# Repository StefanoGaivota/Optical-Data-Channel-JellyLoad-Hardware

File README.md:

Jelly Load is touted as one of the most inconvenient (but also most fun) ways of loading data into your 8 bit computer.<br>
The concept is the collaborative creation of Dave Curran (Tynemouth Software) and Rod Hull (The Future Was 8 bit).

<br>
Data and clock signals are encoded into a video stream as a matrix of black or white areas.<br>
The receiving interface senses the optical channel bit state and converts the result into an 8 bit data word
for interpretation by the target computer upon receiving valid clock edge.

Take a look here:<br>
https://www.tfw8b.com/introducing-jelly-load/<br>
for a historical account.

The loader binaries for VIC20 can be found here:<br>
https://www.tfw8b.com/wp-content/uploads/2024/09/JellyLoad-VIC20-240908.zip<br>
(different ones depending upon your RAM configuration)

This repository is my own effort at creating a JellyLoad receive interface for Commodore computer user port.

It comprises two separate boards which connect to each other via a 14way IDC cable assembly along with associated opto-mechanical components.<br>
KiCAD source is available for schematic and PCB of each board.<br>
FreeCAD source is available for the mechanical elements (Optical Housing and Monitor Guide).<br>
Manufacturing data generated from these sources is detailed later in this document.<br><br>
<p><u><b>Printed Circuit Board parts</u></b></p><br>

* Optical Interface board:

Phototransistors are arranged in the required matrix, photocurrent converted to voltage at input of Schmitt inverter. Inverter outputs are routed to 14 Way IDC.<br>
Clock signal is indicated by an LED for visual feedback of correct operation.<br>
Originally developed to use the OSRAM SFH3710 phototransistor, this seems to be superceded by the SFH3716 (as of December 2025).  Should be a drop-in replacement but YMMV.
<br><br>

* Target Interface board:

Target interface connects the 14Way IDC pins and routes logic signals to target computer User Port connector.<br>
Solder blob config pads route the CLK signal to the user port pin required by the target computer.<br>
This differs between PET, VIC20 and C64. Blob your required option.<br>
Board profile is configured to fit inside a C64 cartridge case.<br>
Case mechanics are shown on layer User.Eco1.<br>
PDF of machining dimensions is made available for convenience.<br><br>
<br>
<p><u><b>Mechanical components</u></b></p><br>

* Optical Housing:

The Optical Interface board is fitted with this Optical Housing for the purpose of reducing ambient light interference and to help align with the optical channel.<br>
Optical aperture adaptors (glass spheres) are accommodated in this section to match the sensor aperture to the available width. A specification for suitable spheres is available in the mechanical data directory. Basically 6.0mm glass balls of good optical clarity.<br>
The graphical calculations shown here are based on a refractive index of 1.4.<br>

<br>
The sensor array will work adequately without the aperture adaptors but sensitivity will be reduced so you will need to use higher monitor brightness for reliable transmission. <br>
The housing can be secured to the sensor board with your adhesive of choice, (sticky tape, cyanoacrylate, blu-tack, toffee etc) or careful heat-staking of the retaining lugs.<br><br>

* Monitor Guide:

The Monitor Guide is attached to the receiving monitor screen, aligned with the appropriately scaled JellyLoad optical channel.<br><br>

<p><u><b>Manufacturing Data</u></b></p><br>

Manufacturing Data for production of Printed Circuit Boards and 3D printed mechanics is available in the "Manufacturing Data" folder.<br>

Bill-Of-Materials (BOM) with Digikey stock codes. BOM and pick/place files for use with JLC (A cheap and cheerful PCB Assembly company)<br>
Gerber+Drill zip for PCB manufacture.<br>

Assembly tooling holes are 1.152mm top-left and bottom right of layout. With JLC, specify "Tooling holes added by customer" at assembly stage.<br><br>

STL exports of Optical Housing and Monitor Guide can be used with most additive manufacturing processes.<br><br>

Once assembled, it should all look something like this:<br>

<br>

Then it's time to connect it up and try it out.<br>
Adjust monitor brightness to give reliable transition of CLOCK LED when presented with light or dark segments at the monitor.<br>
A usable Paint application is your friend here!
<br><br>
A selection of JellyLoad encoded videos can be found here:<br>
https://www.youtube.com/playlist?list=PLbE6E7xnjkkJwXpoj5DF8uXBsocBH2ZH-
<br><br>

Please feel free to get in touch if there's anything you'd like to ask about relating to this repository.<br>
I'm on:<br>
Bluesky  https://bsky.app/profile/stefanogaivota.bsky.social <br>
and <br>
Fedi     https://universeodon.com/@StefanoGaivota<br>
<br>
Best of luck!

</body>

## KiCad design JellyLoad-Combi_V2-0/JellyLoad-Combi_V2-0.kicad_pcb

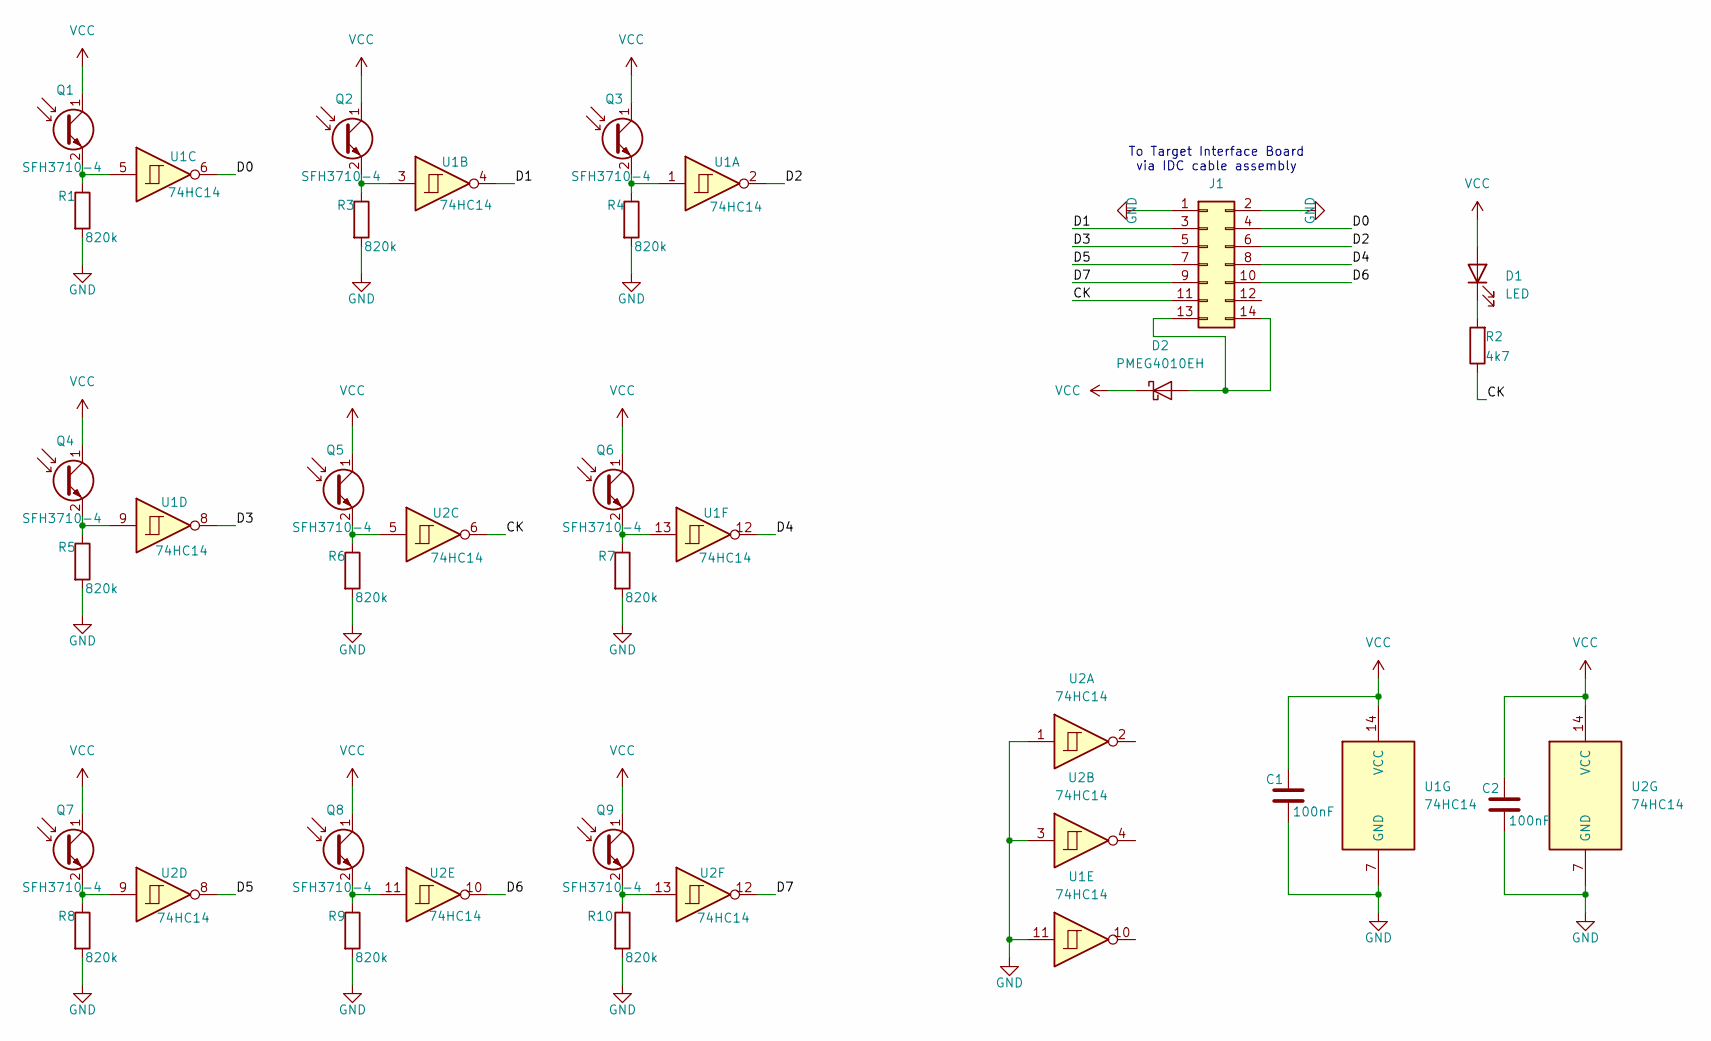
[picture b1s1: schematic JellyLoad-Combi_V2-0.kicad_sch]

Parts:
C1, C2: 100nF; C_0402_1005Metric
D1: LED; LED_0603_1608Metric; JLC PN C19273151
D2: PMEG4010EH; D_SOD-123F; JLC PN C2999987
J1: Conn_02x07_Odd_Even; IDC-Header_2x07_P2.54mm_Vertical; JLC PN C11215
Q1, Q2, Q3, Q4, Q5, Q6, Q7, Q8, Q9: SFH3710-4; Osram_SFH3710
R1, R3, R4, R5, R6, R7, R8, R9, R10: 820k; R_0402_1005Metric; JLC PN C144706
R2: 4k7; R_0402_1005Metric; JLC PN C138287
U1, U2: 74HC14; TSSOP-14_4.4x5mm_P0.65mm; JLC PN C6821

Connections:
/CK: J1.11, R2.1, U2.6
/D0: J1.4, U1.6
/D1: J1.3, U1.4
/D2: J1.6, U1.2
/D3: J1.5, U1.8
/D4: J1.8, U1.12
/D5: J1.7, U2.8
/D6: J1.10, U2.10
/D7: J1.9, U2.12
GND: C1.2, C2.2, J1.1, J1.2, R1.2, R3.2, R4.2, R5.2, R6.2, R7.2, R8.2, R9.2, R10.2, U1.7 (GND), U1.11, U2.1, U2.3, U2.7 (GND)
unnamed: D1.1 (K), R2.2
unnamed: D2.2 (A), J1.13, J1.14
unnamed: Q1.2 (E), R1.1, U1.5
unnamed: Q2.2 (E), R3.1, U1.3
unnamed: Q3.2 (E), R4.1, U1.1
unnamed: Q4.2 (E), R5.1, U1.9
unnamed: Q5.2 (E), R6.1, U2.5
unnamed: Q6.2 (E), R7.1, U1.13
unnamed: Q7.2 (E), R8.1, U2.9
unnamed: Q8.2 (E), R9.1, U2.11
unnamed: Q9.2 (E), R10.1, U2.13
VCC: C1.1, C2.1, D1.2 (A), D2.1 (K), Q1.1 (C), Q2.1 (C), Q3.1 (C), Q4.1 (C), Q5.1 (C), Q6.1 (C), Q7.1 (C), Q8.1 (C), Q9.1 (C), U1.14 (VCC), U2.14 (VCC)

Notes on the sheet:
To Target Interface Board via IDC cable assembly

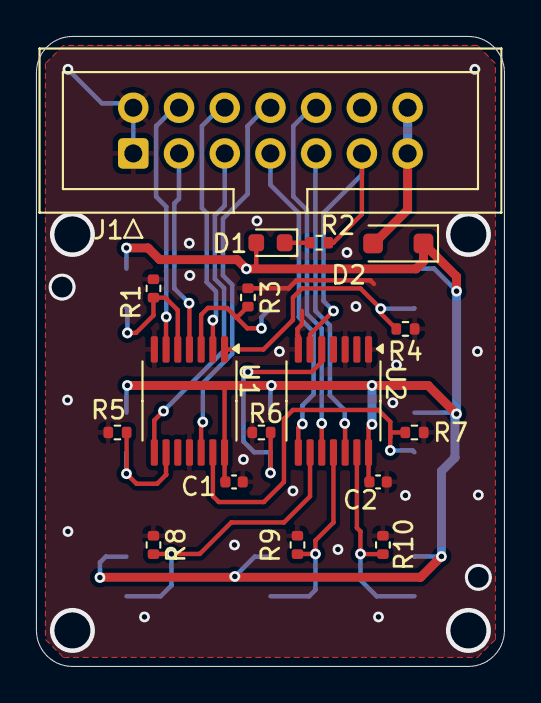
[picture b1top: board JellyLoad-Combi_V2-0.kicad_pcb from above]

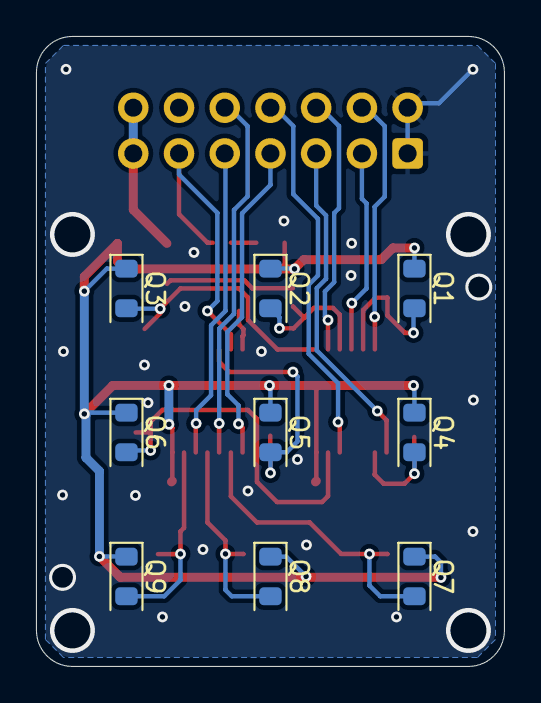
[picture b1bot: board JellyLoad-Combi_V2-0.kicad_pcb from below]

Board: 2 copper layers, 26.0 x 35.0 mm, 26 parts (9 on the bottom side), 22 nets.

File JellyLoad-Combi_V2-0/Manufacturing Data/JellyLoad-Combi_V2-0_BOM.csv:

"Reference","Value","Qty","JLC PN","DK-PN"
"C1,C2","100nF","2","","490-6328-1-ND"
"D1","LED","1","C19273151","732-4978-1-ND"
"D2","PMEG4010EH","1","C2999987","1727-3880-1-ND"
"J1","Conn_02x07_Odd_Even","1","C11215","2987-CH87142V201-ND"
"Q1,Q2,Q3,Q4,Q5,Q6,Q7,Q8,Q9","SFH3710-4","9","","475-SFH3710-3/4-ZCT-ND"
"R1,R3,R4,R5,R6,R7,R8,R9,R10","820k","9","C144706",""
"R2","4k7","1","C138287",""
"U1,U2","74HC14","2","C6821","296-8234-1-ND"

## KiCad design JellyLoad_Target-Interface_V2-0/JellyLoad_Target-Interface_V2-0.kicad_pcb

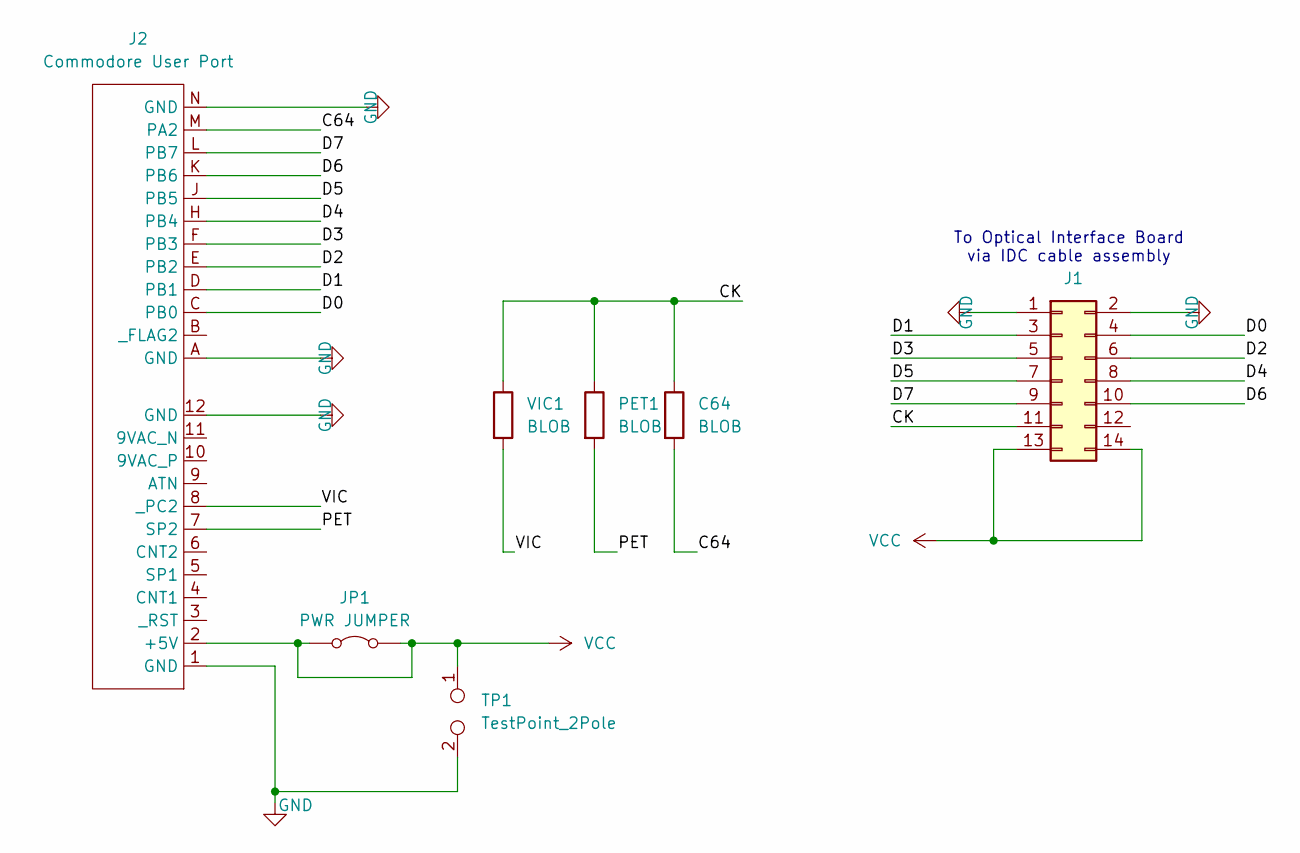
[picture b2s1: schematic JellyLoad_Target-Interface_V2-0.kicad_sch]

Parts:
C64: BLOB; SolderJumper-2_P1.3mm_Open_RoundedPad1.0x1.5mm
J1: Conn_02x07_Odd_Even; IDC-Header_2x07_P2.54mm_Vertical; JLC PN 571-1761681-5
J2: Commodore User Port; Commodore-UserPort-Connector; JLC PN 587-307-024 (Stupidly expensive, try Sw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
JP1: PWR JUMPER; R_1206_3216Metric
PET1: BLOB; SolderJumper-2_P1.3mm_Open_RoundedPad1.0x1.5mm
TP1: TestPoint_2Pole; PinHeader_1x02_P2.54mm_Vertical
VIC1: BLOB; SolderJumper-2_P1.3mm_Open_RoundedPad1.0x1.5mm

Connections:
/C64: C64.2, J2.M (PA2)
/CK: C64.1, J1.11, PET1.1, VIC1.1
/D0: J1.4, J2.C (PB0)
/D1: J1.3, J2.D (PB1)
/D2: J1.6, J2.E (PB2)
/D3: J1.5, J2.F (PB3)
/D4: J1.8, J2.H (PB4)
/D5: J1.7, J2.J (PB5)
/D6: J1.10, J2.K (PB6)
/D7: J1.9, J2.L (PB7)
/PET: J2.7 (SP2), PET1.2
/VIC: J2.8 (_PC2), VIC1.2
GND: J1.1, J1.2, J2.1 (GND), J2.12 (GND), J2.A (GND), J2.N (GND), TP1.2
VCC: J1.13, J1.14, J2.2 (+5V), JP1.1 (A), JP1.2 (B), TP1.1

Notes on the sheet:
To Optical Interface Board via IDC cable assembly

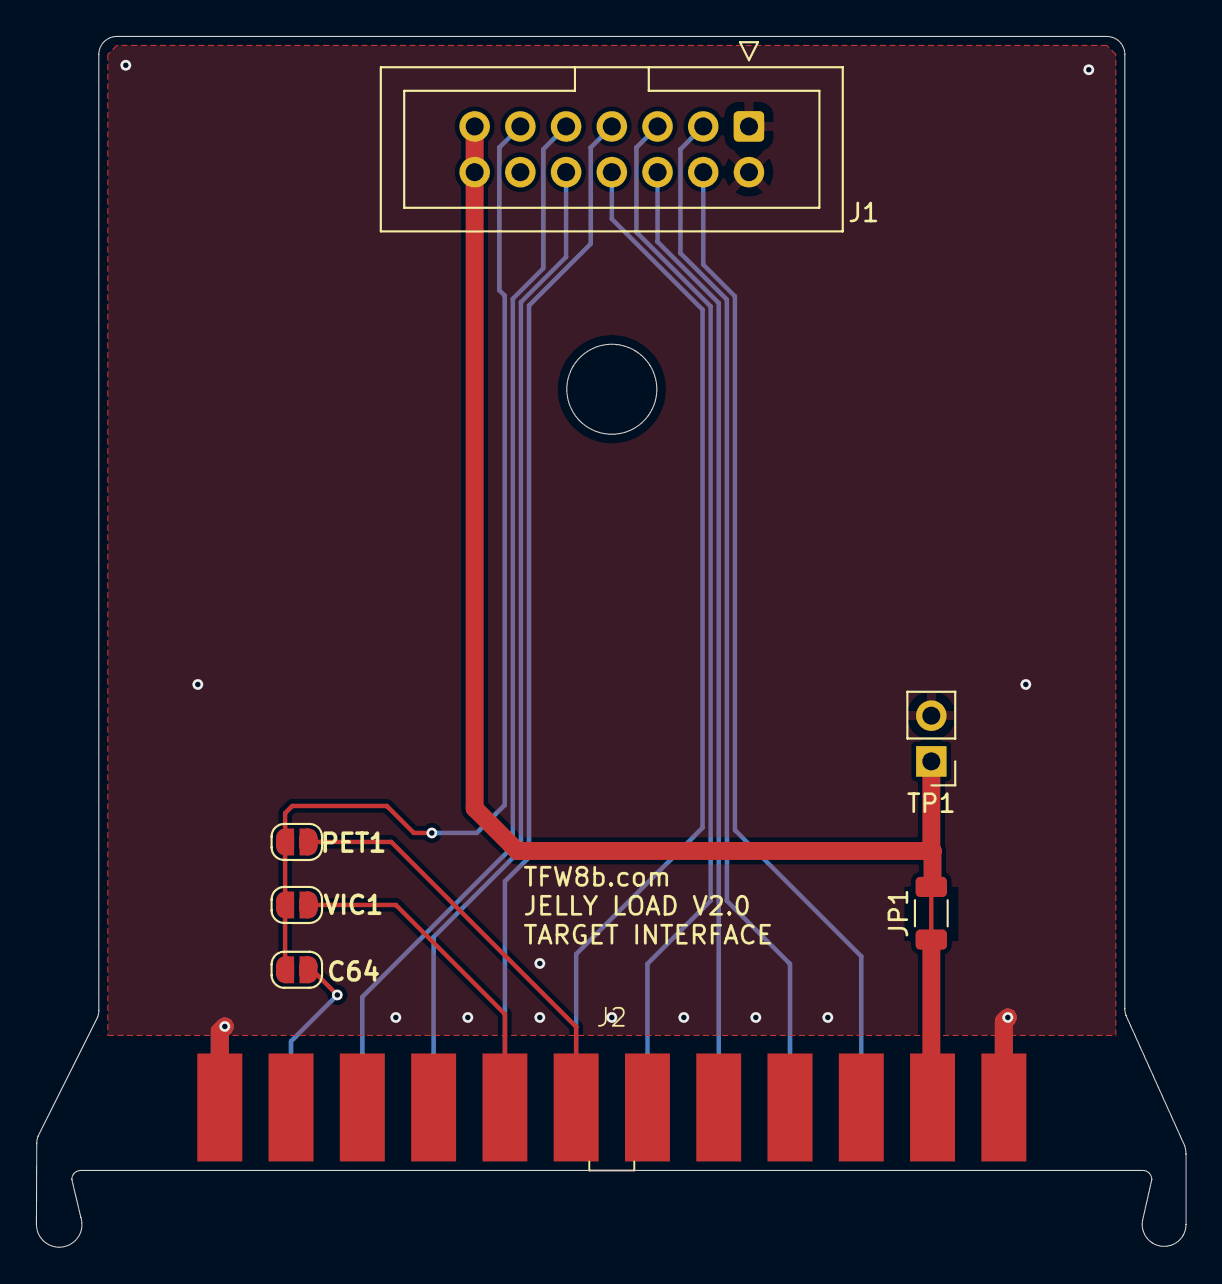
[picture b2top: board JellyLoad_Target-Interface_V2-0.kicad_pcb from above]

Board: 2 copper layers, 63.9 x 67.3 mm, 7 parts (0 on the bottom side), 14 nets.

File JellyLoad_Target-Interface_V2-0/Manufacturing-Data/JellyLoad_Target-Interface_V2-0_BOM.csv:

Reference,Value,Qty,Mouser PN,
J1,Conn_02x07_Odd_Even,1,571-1761681-5,
J2,Commodore User Port,1,587-307-024  (Stupidly expensive, try Switch Electronics)

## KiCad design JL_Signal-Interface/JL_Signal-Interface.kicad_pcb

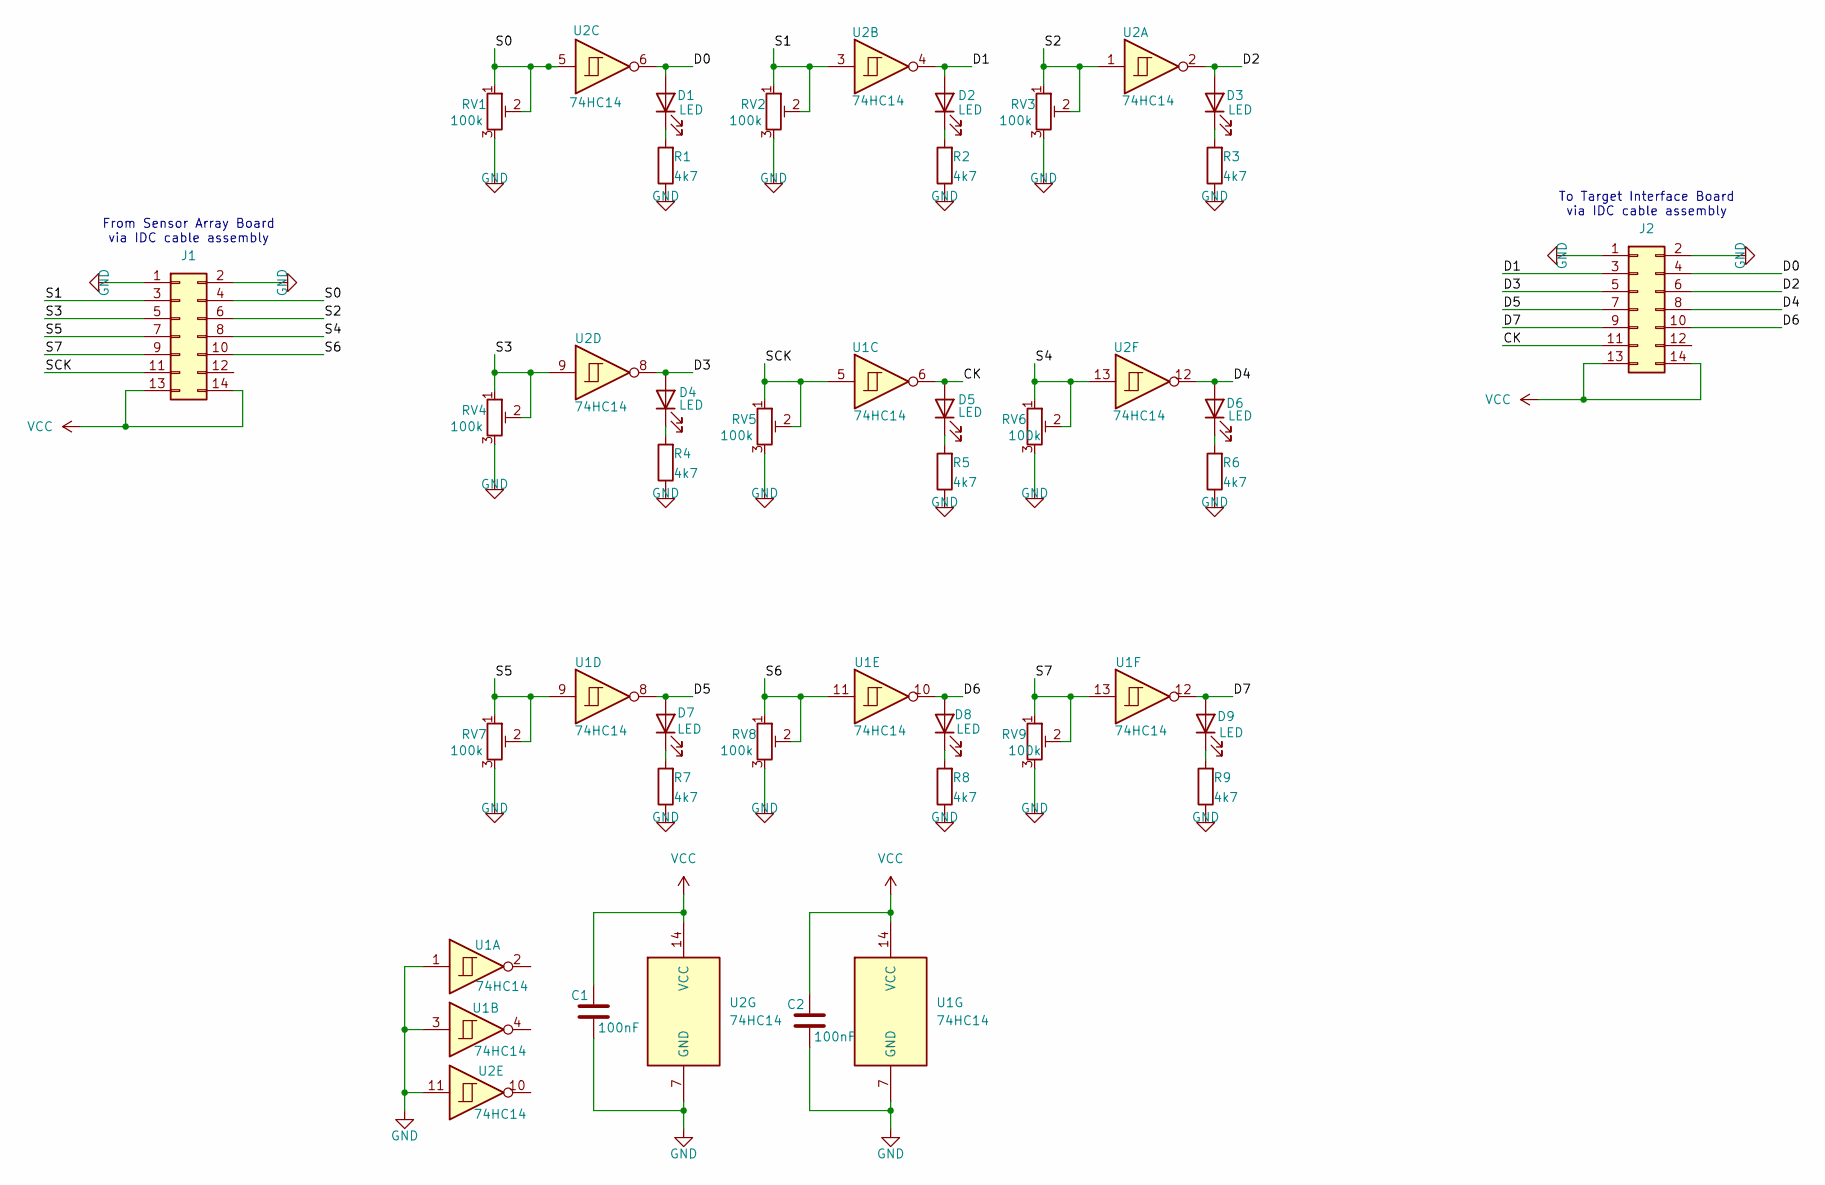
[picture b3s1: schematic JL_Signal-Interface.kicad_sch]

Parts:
C1, C2: 100nF; C_1206_3216Metric_Pad1.33x1.80mm_HandSolder; JLC PN 80-C1206C104K5R7800
D1, D2, D3, D4, D5, D6, D7, D8, D9: LED; LED_1206_3216Metric_Pad1.42x1.75mm_HandSolder; JLC PN 710-150120RS75000
J1, J2: IDC Header 14W; IDC-Header_2x07_P2.54mm_Vertical; JLC PN 571-1761681-5
R1, R2, R3, R4, R5, R6, R7, R8, R9: 4k7; R_1206_3216Metric_Pad1.30x1.75mm_HandSolder; JLC PN 603-RT1206FRE074K7L
RV1, RV2, RV3, RV4, RV5, RV6, RV7, RV8, RV9: 100k; Potentiometer_Bourns_3386F_Vertical; JLC PN 652-3306P-1-104
U1, U2: 74HC14; SOIC-14_3.9x8.7mm_P1.27mm; JLC PN 771-74HC14D-T

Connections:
/CK: D5.2 (A), J2.11, U1.6
/D0: D1.2 (A), J2.4, U2.6
/D1: D2.2 (A), J2.3, U2.4
/D2: D3.2 (A), J2.6, U2.2
/D3: D4.2 (A), J2.5, U2.8
/D4: D6.2 (A), J2.8, U2.12
/D5: D7.2 (A), J2.7, U1.8
/D6: D8.2 (A), J2.10, U1.10
/D7: D9.2 (A), J2.9, U1.12
/S0: J1.4, RV1.1, RV1.2, U2.5
/S1: J1.3, RV2.1, RV2.2, U2.3
/S2: J1.6, RV3.1, RV3.2, U2.1
/S3: J1.5, RV4.1, RV4.2, U2.9
/S4: J1.8, RV6.1, RV6.2, U2.13
/S5: J1.7, RV7.1, RV7.2, U1.9
/S6: J1.10, RV8.1, RV8.2, U1.11
/S7: J1.9, RV9.1, RV9.2, U1.13
/SCK: J1.11, RV5.1, RV5.2, U1.5
GND: C1.2, C2.2, J1.1, J1.2, J2.1, J2.2, R1.1, R2.1, R3.1, R4.1, R5.1, R6.1, R7.1, R8.1, R9.1, RV1.3, RV2.3, RV3.3, RV4.3, RV5.3, RV6.3, RV7.3, RV8.3, RV9.3, U1.1, U1.3, U1.7 (GND), U2.7 (GND), U2.11
unnamed: D1.1 (K), R1.2
unnamed: D2.1 (K), R2.2
unnamed: D3.1 (K), R3.2
unnamed: D4.1 (K), R4.2
unnamed: D5.1 (K), R5.2
unnamed: D6.1 (K), R6.2
unnamed: D7.1 (K), R7.2
unnamed: D8.1 (K), R8.2
unnamed: D9.1 (K), R9.2
VCC: C1.1, C2.1, J1.13, J1.14, J2.13, J2.14, U1.14 (VCC), U2.14 (VCC)

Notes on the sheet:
To Target Interface Board via IDC cable assembly
From Sensor Array Board via IDC cable assembly

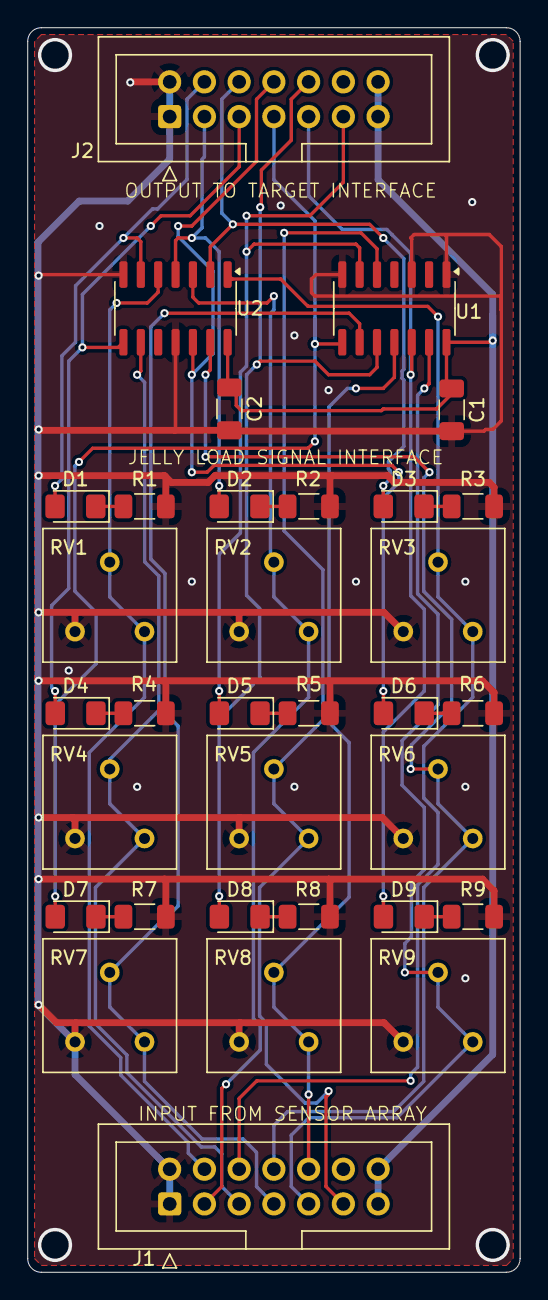
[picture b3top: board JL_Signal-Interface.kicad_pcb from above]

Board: 2 copper layers, 36.0 x 91.0 mm, 33 parts (0 on the bottom side), 29 nets.

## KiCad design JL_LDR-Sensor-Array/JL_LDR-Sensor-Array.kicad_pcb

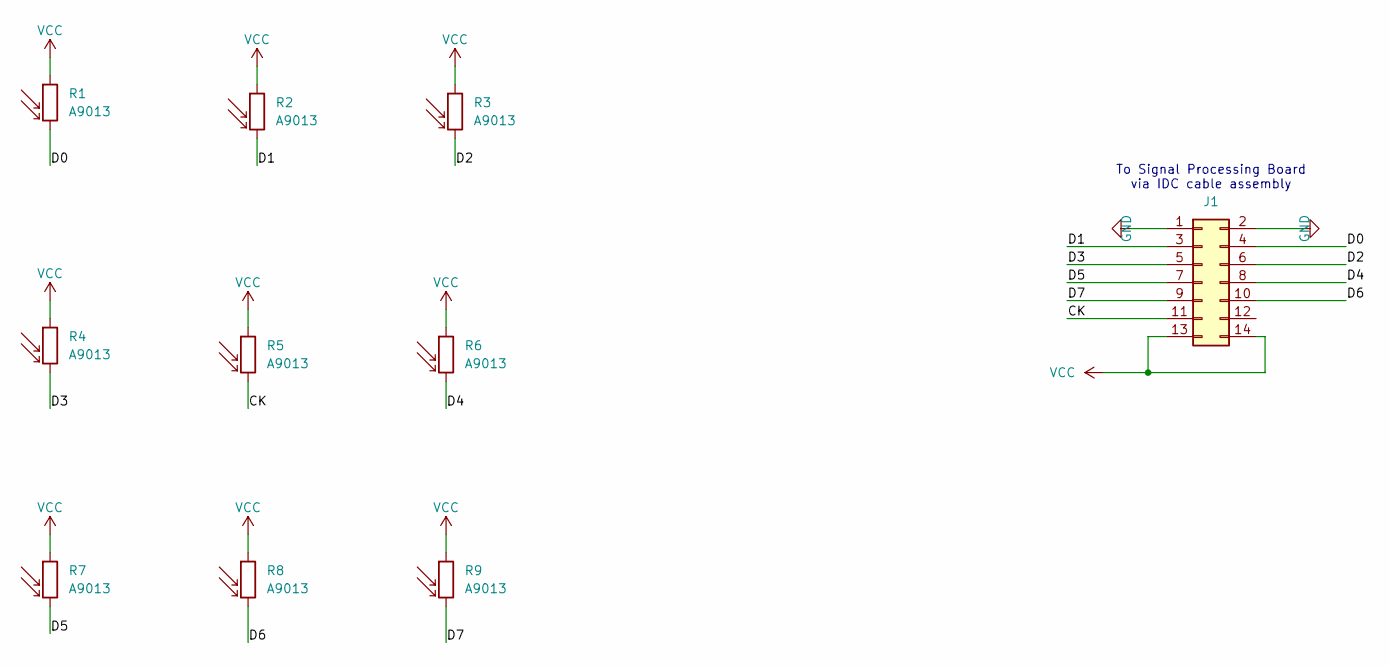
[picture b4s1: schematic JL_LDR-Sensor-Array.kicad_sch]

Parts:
J1: 14W IDC Header; IDC-Header_2x07_P2.54mm_Vertical; JLC PN 571-1761681-5
R1, R2, R3, R4, R5, R6, R7, R8, R9: A9013; R_LDR_5.0x4.1mm_P3mm_Vertical; JLC PN 846-PDV-P8104

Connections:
/CK: J1.11, R5.2
/D0: J1.4, R1.2
/D1: J1.3, R2.2
/D2: J1.6, R3.2
/D3: J1.5, R4.2
/D4: J1.8, R6.2
/D5: J1.7, R7.2
/D6: J1.10, R8.2
/D7: J1.9, R9.2
GND: J1.1, J1.2
VCC: J1.13, J1.14, R1.1, R2.1, R3.1, R4.1, R5.1, R6.1, R7.1, R8.1, R9.1

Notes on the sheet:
To Signal Processing Board via IDC cable assembly

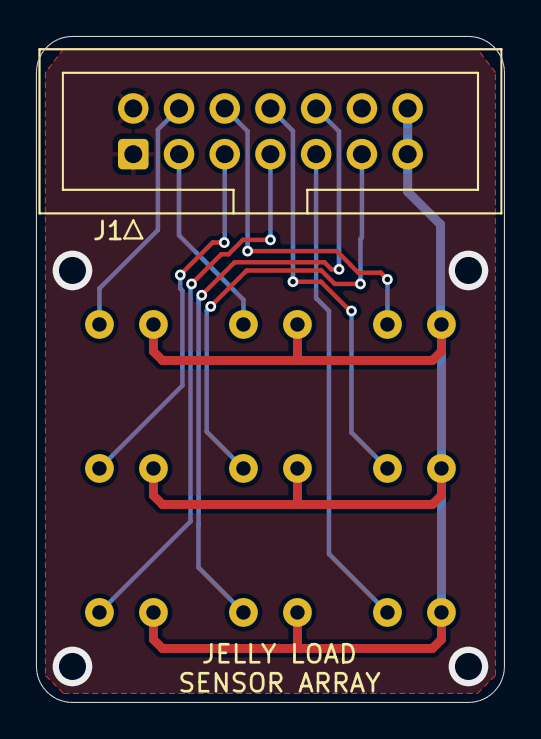
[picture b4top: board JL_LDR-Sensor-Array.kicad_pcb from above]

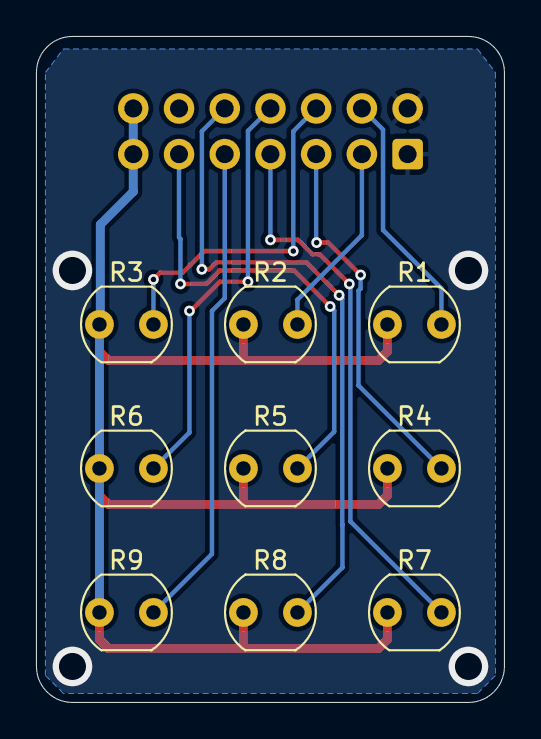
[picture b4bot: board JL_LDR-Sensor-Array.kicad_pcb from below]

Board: 2 copper layers, 26.0 x 37.0 mm, 10 parts (9 on the bottom side), 11 nets.

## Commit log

2024-10-09 KiCAD and manufacturing data uploaded
    LDR Sensor array, Signal Interface and Target Interface boards for JellyLoad system
2024-10-09 Update README.md
    Added some links and creative credits
2024-10-10 Example visualisation added
2024-10-10 Cartridge case machining dimensions
    Dimensions of required cutting for cartridge case to create aperture for IDC connector.
    Based on using 3.175mm diameter cutting tool.
    Reference position is with tool touching top right internal corner as viewed from ABOVE as in the CAD view.
    NOTE: this will be MIRRORED in real life with the case upside down on the toolbed, so ref position shown in this diagram will be TOP LEFT on the toolbed.
    Easier for you to do the mental gymnastics than to reconfigure CAD and end up with something even more confusing.
2024-10-10 Updated Mfr data with better assembly drawing
2024-10-11 Added Mechanical Data for Optical Housing etc
    FreeCAD part design for Jelly Load Optical Housing and Monitor Guide. Export of STL for each part for use in additive manufacture process.
2024-10-11 Updated README.md
    Tried to add GIF of Jelly Load video excerpt
2024-10-11 Update README.md
    Added illustrations of system elements.
    Added description of mechanical elements.
2024-10-11 Update README.md
    Formatted to show illustrations of system parts
2024-10-11 Update README.md
    Formatting update
2024-10-11 Update README.md
    Formatting updates
2024-10-11 Update README.md
    Formatting updates (third time's a charm?)
2024-10-11 Update README.md
    Formatting updates. Turns out third time wasn't a charm. Ho hum.
2024-10-15 Monitor Guide updated
    Monitor Guide crenellations to avoid clashing with IDC solder terminals. Upper faces filleted to smooth sharp edges
2024-10-16 Update to Optical Housing Illustration
    Optical Housing illustration updated to same display type as Monitor Guide piece
2024-10-17 Create LICENSE
    MIT open source, do what you like with it licence.
2024-10-24 Combi phototransistor sensor array
    Combined sensor array based on Osram SFH3710-4 phototransistor along with Schmitt inverters and shunts on the same board. This connects directly to the target interface. Optical characteristics will 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
2024-10-25 Update Optical Housing and Monitor Guide
    Optical Housing and Monitor Guide updated to accommodate and retain aperture matching optics for 2.0mm phototransistor.
2024-11-01 Monitor guide apertures widened
    Apertures widened to accommodate optical transformer spheres used with phototransistor variant
2024-11-01 Create Optical sphere specification
    Basic specification for optical interfacing spheres to better match SFH3710 aperture to the monitor guide.
2024-11-01 Link to VIC20 loader binaries
    Added link to the VIC20 loader binaries
2024-11-01 Update README.md
    Formatting and references to phototransistor combi variant
2024-11-02 Adjusted Optical Housing retaining lip
    Made the retaining lip thicker for simpler manufacture.
2024-11-15 Drill file and bottom copper update
    Corner mounting holes widened to 2.0mm for more robust mechanics. Added 2x tooling holes (1.152mm) for assembly process.
2024-11-15 Layout updates for manufacture process
    Corner mounting holes widened to 2.0mm for more robust mechanics. Added 2x tooling holes (1.152mm) for assembly process.
2024-11-15 Thicker corner lugs, reduced vertical clearance
    Corner retaining lugs widened to 1.9mm for improved robustness. Clearance from aperture translator sphere to sensor reduced to 1.1mm to reduce rattle.
2024-11-15 Delete JL_LDR-Sensor-Array directory
    LDR sensor is too slow. Removing to simplify manufacture options.
2024-11-15 Delete JL_Signal-Interface directory
    Removing LDR option for simplicity. Signal interface board no longer necessary.
2024-11-15 Updated Drill and bottom copper
    Corner holes widened to 2.0mm, added 2x tooling holes (1.152mm) for assembly process.
2024-11-15 Combi board visualisation
    Eyecandy of combi board.
2024-11-15 Updated illustrations of mechanics
2024-11-15 Update README.md to reflect recent changes
    Project simplification. Narrative flow through to manufacturing processes.
2024-11-17 Photograph of Version 2.0 Hardware
2024-11-19 Admin updates to schematic and layout
2024-11-19 Added schematic PDF output and assembly drawing
2025-12-05 Create placeholder
2025-12-05 Manufacturing data all in one place
    Manfuacturing data (Gerbers, BOMs and component placements) for Sensor array board and Target Interface board
    STL (3D Print ) data for Monitor Guide and Optical Housing mechanics.
2025-12-05 Optical Array Assembly Drawing
2025-12-05 Updated assembly drawing
    Assembly drawing updated to better show orientation of SFH3710 photo-transistors
2025-12-05 Updates to README.md
    Updated README to refer directly to Manufacturing Data folder.
2025-12-06 Updated Sensor Array MDP
2025-12-06 Delete Manufacturing-Data/JellyLoad-Combi-V2-0_Assembly-Drawing.pdf
    Assembly drawing for sensor array now in MDP
2025-12-06 Delete Manufacturing-Data/JellyLoad-Sensor-Board_MDP.zip
    Sensor array MDP updated. Simpler to delete previous version.
2025-12-06 Delete Manufacturing-Data/placeholder
    Removing placeholder used to create folder
2025-12-07 Updated JLC Pick-and-Place data
    Pick and place data revised to show correct orientation and position of J1 connector.
2025-12-10 Sensor array MDP updated
    Sensor array MDP updated to include bottom layer components (phototransistors) and pick-place position data.
2025-12-21 Update to BOM
    LED part numbers changed to be RED LED consistently with JLC and Digikey
2025-12-21 Putting Mfr Data in one place
    Updated BOM and not duplicating manufacture data.
2025-12-21 Mfr tolerance update
2025-12-21 Delete JellyLoad_Target-Interface_V2-0/Manufacturing-Data/JellyLoad_Target-Interface_V2-0_BOM.csv
    removing duplicate manufacture data
2025-12-21 Delete JellyLoad_Target-Interface_V2-0/Manufacturing-Data/JellyLoad_Target-Interface_V2-0_Manufacturing-Data.zip
    removing duplicate manufacture data
2025-12-30 Updated illustration
    Optical housing illustration update
2025-12-30 Optical Housing updates
    Added retaining pips to sphere apertures. Consolidated constraints to named references.
2025-12-30 Updates to Optical Housing
    Optical Housing updated to include retaining pips in sphere apertures.
2025-12-30 Update Optical sphere specification
    Added stipulation that glass should clear and not frosted.
2025-12-30 Update README.md
    Corrected error in description: now "Digikey stock codes"
2026-01-02 Adjusted aperture and pips
    Widened aperture to allow easier installation of spheres. Retaining pip position adjusted to give allowance for material deformation.
2026-01-02 Optical housing aperture and pip adjustment
    Updated STL exports based on Optical Housing adjusted aperture and retaining pip positions.
2026-01-05 Clearer illustration of optics calculations
2026-01-14 Thickened retaining pips
    Retaining pip thickness was below print process resolution. Made them thicker so they actually appear in the sliced print output. May need to experiment further with sizing and / or post-print proces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
2026-01-14 Updated STL export
    STL export updated to include thickened retaining pips in Optical Housing model.
2026-01-17 Optical housing illustration update
2026-01-17 Optical housing update
    Updated model to make sphere retention more easily manufactured using FDM processes. Using octagonal pocket for retention diameter then accommodation diameter thereafter. When sliced for FDM, this mo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
2026-01-17 Updated STL model
    Optical housing update for FDM process.
